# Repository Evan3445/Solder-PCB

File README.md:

# Solder-PCB 
# Energyportel

The main function of the PCB is that there is a button which will control the functioning of all the LEDs present in the board. 

## Schematic

## PCB

## How to build
Order the PCB & components, Look at the KiCAD file and build it accordingly.

## BOM
NE555 timer (DIP-8) × 1
Red 5 mm LED × 6
470 Ω resistor × 6
47 kΩ resistor × 4
4.7 kΩ resistor × 1
Photoresistor (LDR) × 1
1 kΩ potentiometer × 1
2N3904 transistor × 2
10 µF capacitor × 2
6 mm push button × 1
CR2032 battery holder × 1
Made by Evan!!

Made as a part of http://solder.hackclub.com/!

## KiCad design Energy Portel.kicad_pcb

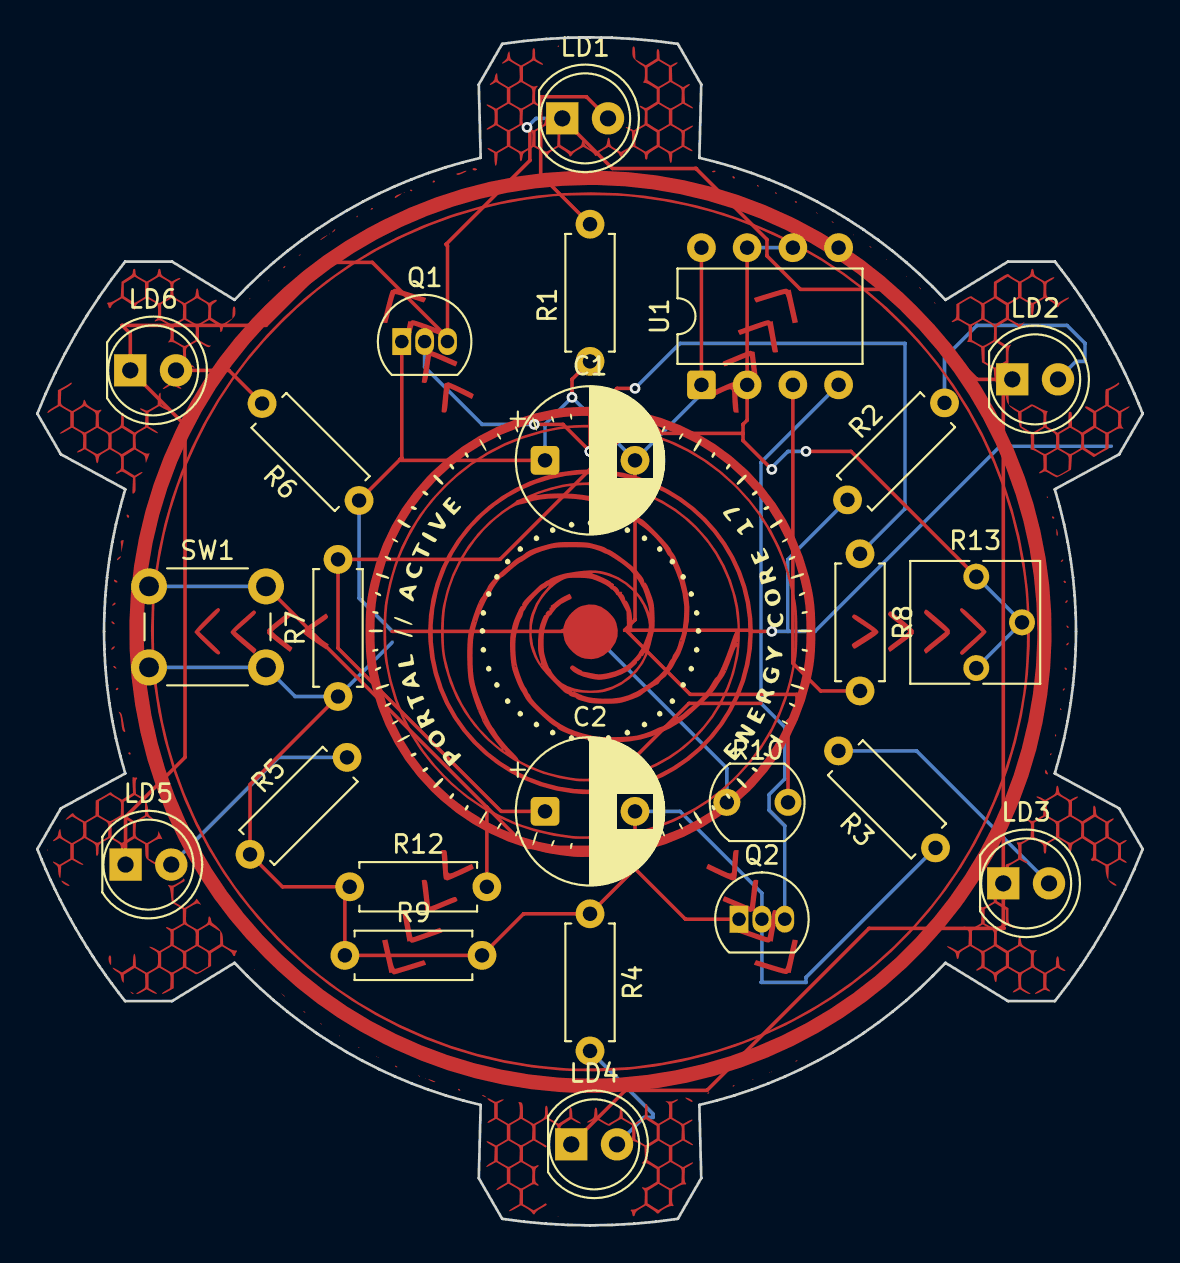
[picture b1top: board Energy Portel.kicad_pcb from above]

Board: 2 copper layers, 61.4 x 66.0 mm, 25 parts (1 on the bottom side), 12 nets.

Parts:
BT1: Battery_Cell; BatteryHolder_Keystone_3034_1x20mm
C1, C2: 10uf; CP_Radial_D8.0mm_P5.00mm
LD1, LD2, LD3, LD4, LD5, LD6: SPL_PL90; LED_D5.0mm
Q1, Q2: 2N3904; TO-92_Inline
R1, R2, R3, R4, R5, R6: 470R; R_Axial_DIN0207_L6.3mm_D2.5mm_P7.62mm_Horizontal
R7, R8: 4.7k; R_Axial_DIN0207_L6.3mm_D2.5mm_P7.62mm_Horizontal
R9, R12: 47k; R_Axial_DIN0207_L6.3mm_D2.5mm_P7.62mm_Horizontal
R10: R_Photo; R_LDR_5.1x4.3mm_P3.4mm_Vertical
R13: Potentiometer; Potentiometer_Vishay_T73YP_Vertical
SW1: SW_Push; SW_PUSH_6mm
U1: NE555D; DIP-8_W7.62mm

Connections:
unnamed: BT1.1 (+), BT1.2 (-), C1.1, C1.2, C2.2, Q1.1 (E), Q2.1 (E), Q2.2 (B), R1.1, R2.1, R3.1, R4.1, R5.1, R6.1, R7.1, R9.1, R9.2, R10.1, R10.2, R12.1, SW1.2, U1.1 (GND), U1.8 (VCC)
unnamed: LD1.2 (A), R1.2
unnamed: LD1.1 (C), LD2.1 (C), LD3.1 (C), LD4.1 (C), LD5.1 (C), LD6.1 (C), Q1.3 (C)
unnamed: LD2.2 (A), R2.2
unnamed: LD3.2 (A), R3.2
unnamed: LD4.2 (A), R4.2
unnamed: LD5.2 (A), R5.2
unnamed: LD6.2 (A), R6.2
unnamed: Q1.2 (B), R8.1
unnamed: Q2.3 (C), R12.2, SW1.1, U1.4 (~RST)
unnamed: C2.1, R7.2, R13.1, R13.2, R13.3, U1.2 (TRIG), U1.6 (THRES), U1.7 (DISCH)
unnamed: R8.2, U1.3 (OUT)
